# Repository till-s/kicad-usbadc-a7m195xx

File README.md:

# 130MSPS Dual-Channel Scope - Hardware Design

Please visit the [super-repository](https://github.com/till-s/ScOpen) for more information about this project.

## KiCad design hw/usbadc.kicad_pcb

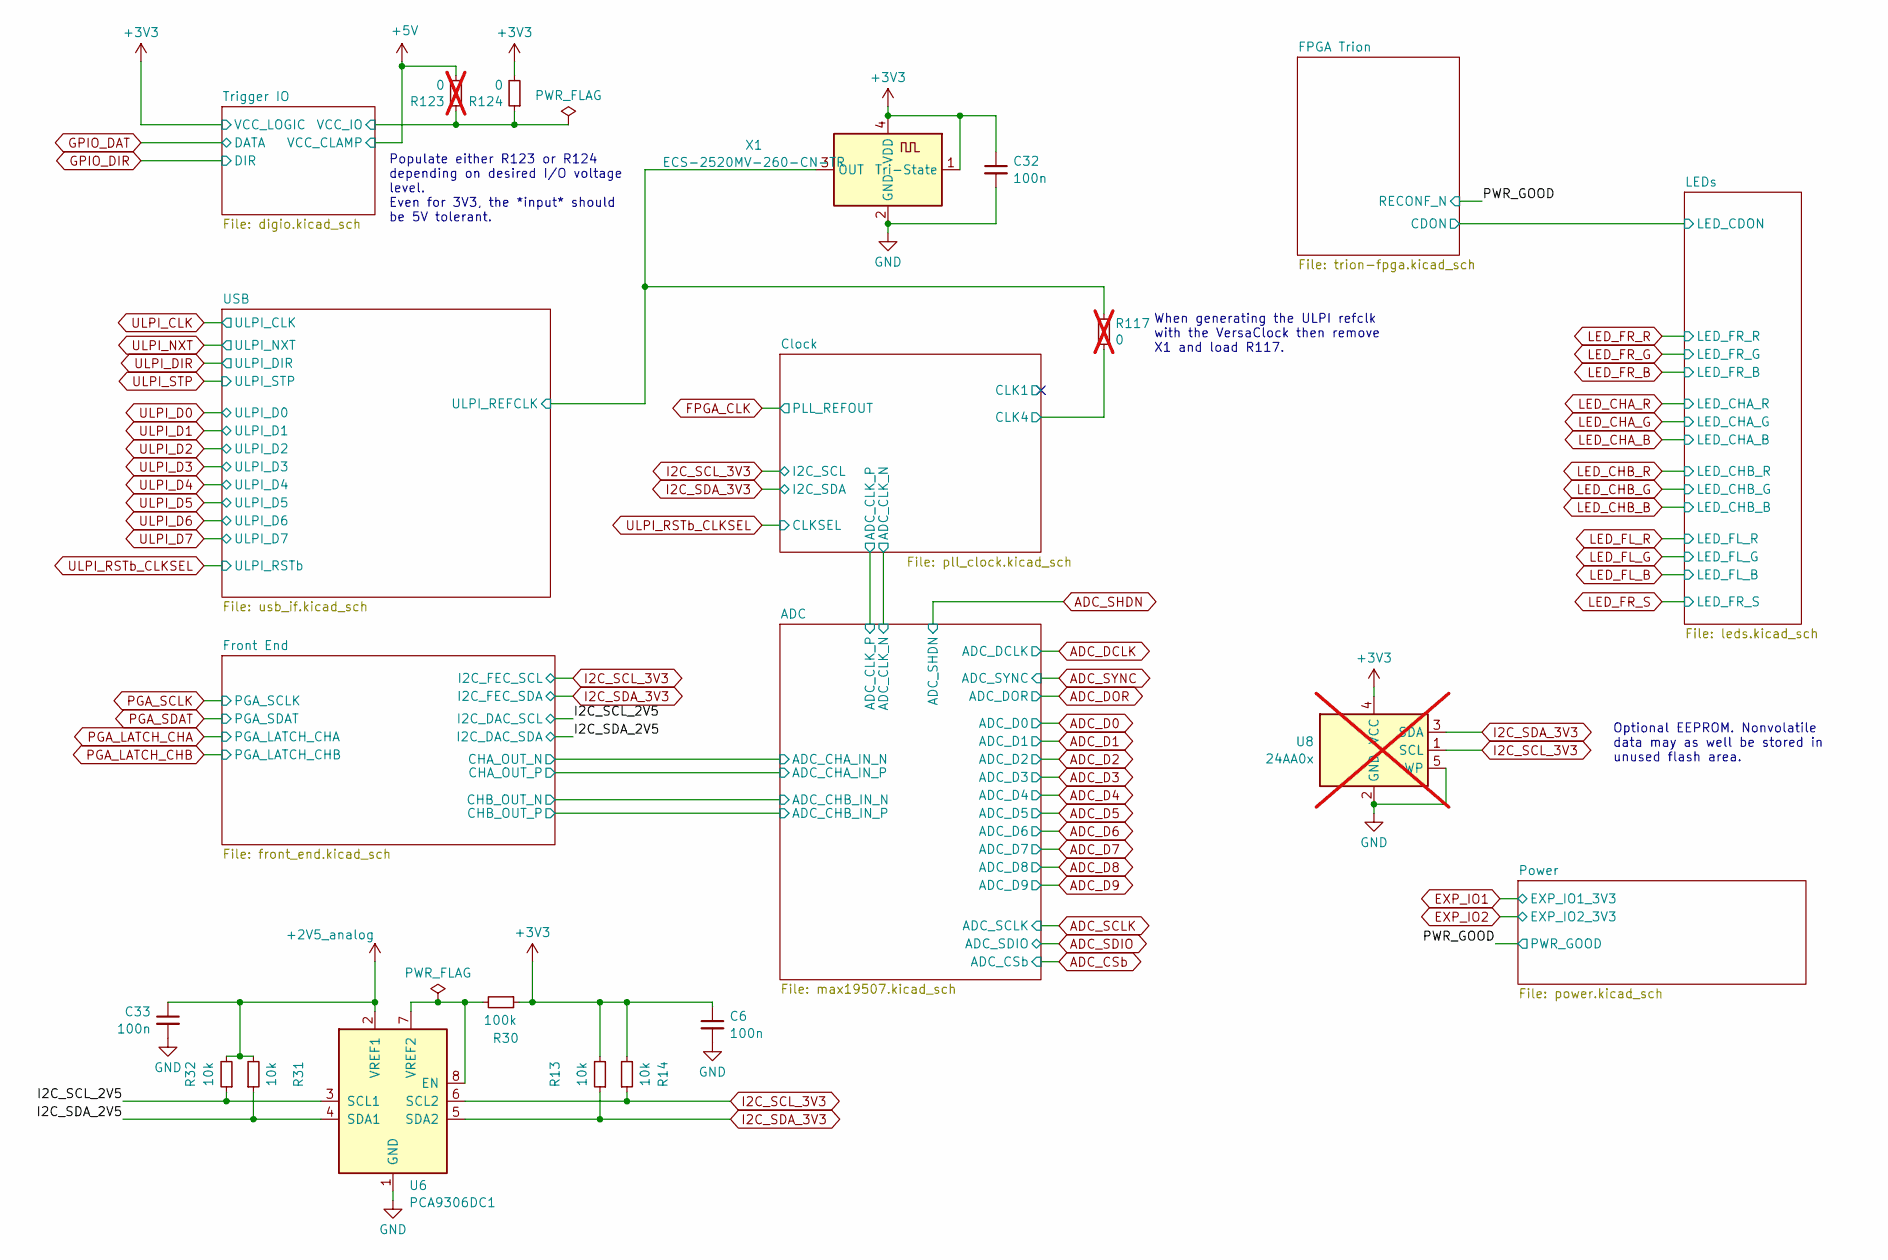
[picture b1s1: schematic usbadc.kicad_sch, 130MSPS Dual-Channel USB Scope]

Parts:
C6, C32, C33: 100n; C_0603_1608Metric; Part CL10B104KB8NFN
R13, R14, R31, R32: 10k; R_0603_1608Metric; Part RMCF0603FT10K0
R30: 100k; R_0603_1608Metric; Part RMCF0603FT100K
R117, R123: 0; R_0603_1608Metric; Part RMCF0603ZT0R00; not fitted
R124: 0; R_0603_1608Metric; Part RMCF0603ZT0R00
U6: PCA9306DC1; VSSOP-8_2.3x2mm_P0.5mm; Part PCA9306TDCURQ1
U8: 24AA0x; SOT-353_SC-70-5; Part 24AA01/LT; not fitted
X1: ECS-2520MV-260-CN-TR; Oscillator_SMD_ECS_2520MV-xxx-xx-4Pin_2.5x2.0mm; Part ECS-2520MV-260-CN-TR

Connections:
+2V5_analog: C33.1, R31.2, R32.2, U6.2 (VREF1); also elsewhere on the board
+3V3: C6.1, C32.1, R13.2, R14.2, R30.1, R124.2, U8.4 (VCC), X1.1 (Tri-State), X1.4 (VDD); also elsewhere on the board
+5V: R123.2; also elsewhere on the board
/Clock/CLK4: R117.2; also elsewhere on the board
/I2C_SCL_2V5: R32.1, U6.3 (SCL1); also elsewhere on the board
/I2C_SDA_2V5: R31.1, U6.4 (SDA1); also elsewhere on the board
/Trigger IO/VCC_IO: R123.1, R124.1; also elsewhere on the board
/USB/ULPI_REFCLK: R117.1, X1.3 (OUT); also elsewhere on the board
GND: C6.2, C32.2, C33.2, U6.1 (GND), U8.2 (GND), U8.5 (WP), X1.2 (GND); also elsewhere on the board
I2C_SCL_3V3: R14.1, U6.6 (SCL2), U8.1 (SCL); also elsewhere on the board
I2C_SDA_3V3: R13.1, U6.5 (SDA2), U8.3 (SDA); also elsewhere on the board
unnamed: R30.2, U6.7 (VREF2), U6.8 (EN)

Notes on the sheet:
Optional EEPROM. Nonvolatile data may as well be stored in unused flash area.
When generating the ULPI refclk with the VersaClock then remove X1 and load R117.
Populate either R123 or R124 depending on desired I/O voltage level. Even for 3V3, the *input* should be 5V tolerant.

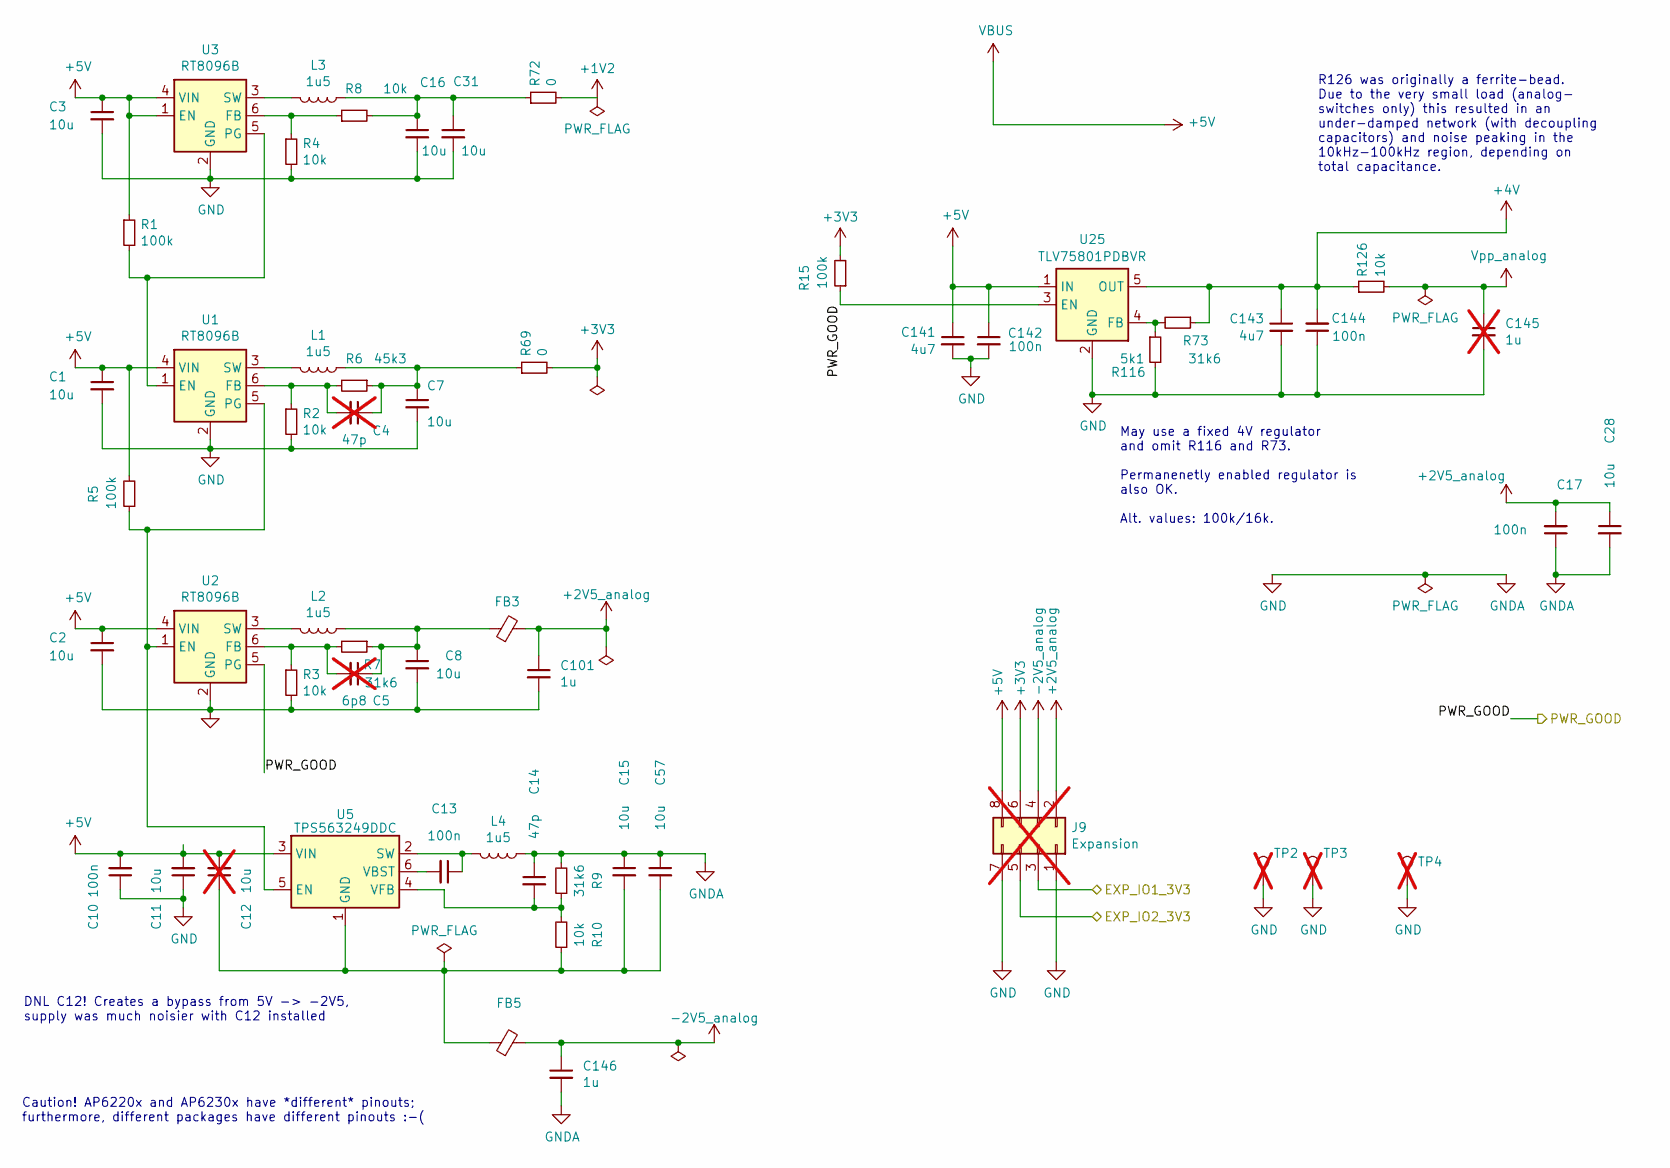
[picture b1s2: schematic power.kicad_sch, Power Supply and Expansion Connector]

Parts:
C1, C2, C3, C7, C8, C11, C15, C16, C28, C31, C57: 10u; C_1206_3216Metric; Part CL31A106KPHNNNE
C4: 47p; C_0603_1608Metric; Part 0603N470J101CT; not fitted
C5: 6p8; C_0603_1608Metric; Part 885012006050; not fitted
C10, C13, C17, C142, C144: 100n; C_0603_1608Metric; Part CL10B104KB8NFN
C12: 10u; C_1206_3216Metric; Part CL31A106KPHNNNE; not fitted
C14: 47p; C_0603_1608Metric; Part 0603N470J101CT
C101, C146: 1u; C_0805_2012Metric; Part CGA4J2X7R1C105K125AA
C141, C143: 4u7; C_0805_2012Metric; Part 2012X5R1C475K125AC
C145: 1u; C_0805_2012Metric; Part CGA4J2X7R1C105K125AA; not fitted
FB3, FB5: 600Ohm@100MHz; L_0603_1608Metric; Part MI0603J601R-10
J9: Expansion; PinHeader_2x04_P2.54mm_Vertical; not fitted
L1, L2, L3, L4: 1u5; L_1008_2520Metric; Part BDCD002520121R5MS1
R1, R5, R15: 100k; R_0603_1608Metric; Part RMCF0603FT100K
R2, R3, R4, R8, R10, R126: 10k; R_0603_1608Metric; Part RMCF0603FT10K0
R6: 45k3; R_0603_1608Metric; Part RMCF0603FT45K3
R7, R9, R73: 31k6; R_0603_1608Metric; Part RMCF0603FT31K6
R69, R72: 0; R_0603_1608Metric; Part RMCF0603ZT0R00
R116: 5k1; R_0603_1608Metric; Part RMCF0603FT5K10
TP2, TP3, TP4: TestPoint; PinHeader_1x01_P2.54mm_Vertical; not fitted
U1, U2, U3: RT8096B; SOT-23-6; Part RT8096BHGE
U5: TPS563249DDC; SOT-23-6; Part TPS563249DDCR
U25: TLV75801PDBVR; SOT-23-5; Part TLV75801PDBVR

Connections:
+1V2: R72.2; also elsewhere on the board
+2V5_analog: C17.2, C28.1, C101.1, FB3.2, J9.2; also elsewhere on the board
+3V3: J9.6, R15.2, R69.2; also elsewhere on the board
+4V: C143.1, C144.2, R73.1, R126.1, U25.5 (OUT); also elsewhere on the board
+5V: C1.1, C2.1, C3.1, C10.2, C11.2, C12.2, C141.1, C142.1, J9.8, R1.1, R5.2, U1.4 (VIN), U2.4 (VIN), U3.1 (EN), U3.4 (VIN), U5.3 (VIN), U25.1 (IN); also elsewhere on the board
-2V5_analog: C146.1, FB5.2, J9.4; also elsewhere on the board
/PWR_GOOD: R15.1, U2.5 (PG), U25.3 (EN); also elsewhere on the board
EXP_IO1: J9.3; also elsewhere on the board
EXP_IO2: J9.5; also elsewhere on the board
GND: C1.2, C2.2, C3.2, C7.2, C8.2, C10.1, C11.1, C14.1, C15.1, C16.2, C17.1, C28.2, C31.2, C57.1, C101.2, C141.2, C142.2, C143.2, C144.1, C145.2, C146.2, J9.1, J9.7, L4.1, R2.2, R3.2, R4.2, R9.2, R116.2, TP2.1, TP3.1, TP4.1, U1.2 (GND), U2.2 (GND), U3.2 (GND), U25.2 (GND); also elsewhere on the board
unnamed: C4.1, C7.1, L1.1, R6.1, R69.1
unnamed: C5.1, C8.1, FB3.1, L2.1, R7.1
unnamed: C16.1, C31.1, L3.1, R8.2, R72.1
unnamed: R1.2, U1.1 (EN), U3.5 (PG)
unnamed: C4.2, R2.1, R6.2, U1.6 (FB)
unnamed: R5.1, U1.5 (PG), U2.1 (EN), U5.5 (EN)
unnamed: L1.2, U1.3 (SW)
unnamed: C5.2, R3.1, R7.2, U2.6 (FB)
unnamed: L2.2, U2.3 (SW)
unnamed: R4.1, R8.1, U3.6 (FB)
unnamed: L3.2, U3.3 (SW)
unnamed: C12.1, C15.2, C57.2, FB5.1, R10.1, U5.1 (GND)
unnamed: C13.1, L4.2, U5.2 (SW)
unnamed: C13.2, U5.6 (VBST)
unnamed: C14.2, R9.1, R10.2, U5.4 (VFB)
unnamed: R73.2, R116.1, U25.4 (FB)
Vpp_analog: C145.1, R126.2; also elsewhere on the board

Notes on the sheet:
May use a fixed 4V regulator and omit R116 and R73. Permanenetly enabled regulator is also OK. Alt. values: 100k/16k.
R126 was originally a ferrite-bead. Due to the very small load (analog- switches only) this resulted in an under-damped network (with decoupling capacitors) and noise peaking in the 10kHz-100kHz region, depending on total capacitance.
DNL C12! Creates a bypass from 5V -> -2V5, supply was much noisier with C12 installed
Caution! AP6220x and AP6230x have *different* pinouts; furthermore, different packages have different pinouts :-(

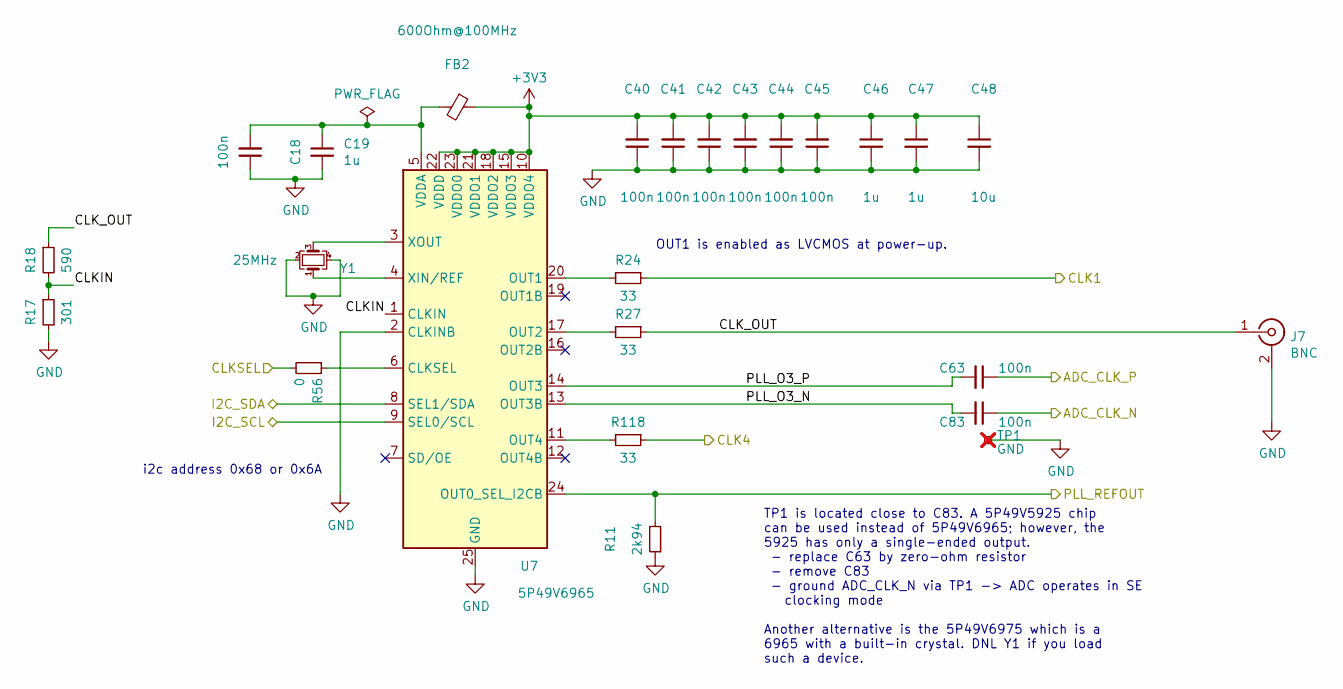
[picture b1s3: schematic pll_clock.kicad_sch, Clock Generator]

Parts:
C18, C40, C41, C42, C43, C44, C45, C63, C83: 100n; C_0603_1608Metric; Part CL10B104KB8NFN
C19, C46, C47: 1u; C_0805_2012Metric; Part CGA4J2X7R1C105K125AA
C48: 10u; C_1206_3216Metric; Part CL31A106KPHNNNE
FB2: 600Ohm@100MHz; L_0603_1608Metric; Part MI0603J601R-10
J7: BNC; BNC_Molex_0731713150; Part 0731713150
R11: 2k94; R_0603_1608Metric; Part RMCF0603FT2K94
R17: 301; R_0603_1608Metric; Part RMCF0603FT301R
R18: 590; R_0603_1608Metric; Part RMCF0603FT590R
R24, R27, R118: 33; R_0603_1608Metric; Part RMCF0603FT33R0
R56: 0; R_0603_1608Metric; Part RMCF0603ZT0R00
TP1: GND; single_pad; not fitted
U7: 5P49V6965; QFN-24-1EP_4x4mm_P0.5mm_EP2.8x2.8mm; Part 5P49V6965A000NLGI8
Y1: 25MHz; Crystal_SMD_Abracon_ABM10-4Pin_2.5x2.0mm; Part ABM10W-25.0000MHZ-8-B1U-T3

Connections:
+3V3: C40.2, C41.2, C42.2, C43.2, C44.2, C45.2, C46.1, C47.1, C48.1, FB2.1, U7.10 (VDDO4), U7.15 (VDDO3), U7.18 (VDDO2), U7.21 (VDDO1), U7.22 (VDDD), U7.23 (VDDO0); also elsewhere on the board
/ADC/ADC_CLK_N: C83.1; also elsewhere on the board
/ADC/ADC_CLK_P: C63.1; also elsewhere on the board
/Clock/CLK1: R24.1
/Clock/CLK4: R118.1; also elsewhere on the board
/Clock/CLKIN: R17.1, R18.2, U7.1 (CLKIN)
/Clock/CLK_OUT: J7.1 (In), R18.1, R27.1
/Clock/PLL_O3_N: C83.2, U7.13 (OUT3B)
/Clock/PLL_O3_P: C63.2, U7.14 (OUT3)
FPGA_CLK: R11.2, U7.24 (OUT0_SEL_I2CB); also elsewhere on the board
GND: C18.1, C19.2, C40.1, C41.1, C42.1, C43.1, C44.1, C45.1, C46.2, C47.2, C48.2, J7.2 (Ext), R11.1, R17.2, TP1.1, U7.2 (CLKINB), U7.25 (GND), Y1.2, Y1.4; also elsewhere on the board
I2C_SCL_3V3: U7.9 (SEL0/SCL); also elsewhere on the board
I2C_SDA_3V3: U7.8 (SEL1/SDA); also elsewhere on the board
unnamed: R56.1, U7.6 (CLKSEL)
unnamed: R24.2, U7.20 (OUT1)
unnamed: R27.2, U7.17 (OUT2)
unnamed: R118.2, U7.11 (OUT4)
unnamed: C18.2, C19.1, FB2.2, U7.5 (VDDA)
unnamed: U7.4 (XIN/REF), Y1.1
unnamed: U7.3 (XOUT), Y1.3
ULPI_RSTb_CLKSEL: R56.2; also elsewhere on the board

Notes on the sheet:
TP1 is located close to C83. A 5P49V5925 chip can be used instead of 5P49V6965; however, the 5925 has only a single-ended output. - replace C63 by zero-ohm resistor - remove C83 - ground ADC_CLK_N via TP1 -> ADC operates in SE clocking mode Another alternative is the 5P49V6975 which is a 6965 with 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
i2c address 0x68 or 0x6A
OUT1 is enabled as LVCMOS at power-up.

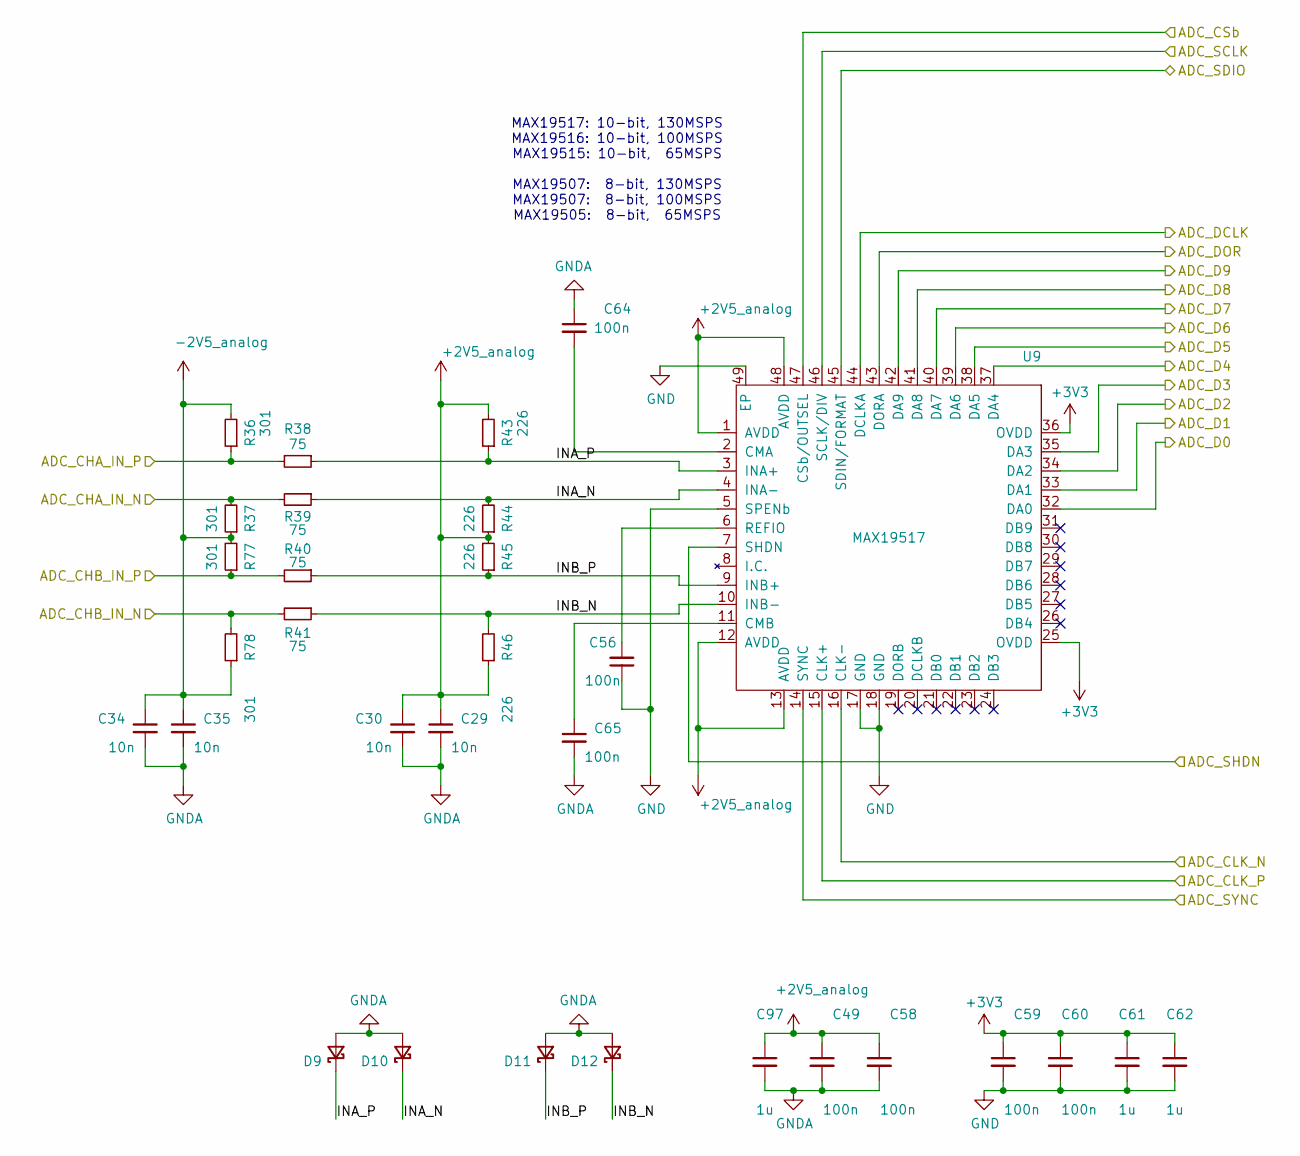
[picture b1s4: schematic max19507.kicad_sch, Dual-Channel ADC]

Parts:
C29, C30, C34, C35: 10n; C_0603_1608Metric; Part C0603C103J5RACTU
C49, C58, C59, C60: 100n; C_0402_1005Metric; Part C1005X7R1E104K050BB
C56, C64, C65: 100n; C_0603_1608Metric; Part CL10B104KB8NFN
C61, C62, C97: 1u; C_0805_2012Metric; Part CGA4J2X7R1C105K125AA
D9, D10, D11, D12: NSR0170HT1G; D_SOD-323; Part NSR0170HT1G
R36, R37, R77, R78: 301; R_0603_1608Metric; Part RMCF0603FT301R
R38, R39, R40, R41: 75; R_0603_1608Metric; Part RMCF0603FT75R0
R43, R44, R45, R46: 226; R_0603_1608Metric; Part RMCF0603FT226R
U9: MAX19517; QFN-48-1EP_7x7mm_P0.5mm_EP5.6x5.6mm_ThermalVias_biggerholes; Part MAX19517ETM+

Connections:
+2V5_analog: C29.1, C30.1, C49.1, C58.1, C97.1, R43.2, R44.1, R45.2, R46.1, U9.1 (AVDD), U9.12 (AVDD), U9.13 (AVDD), U9.48 (AVDD); also elsewhere on the board
+3V3: C59.1, C60.1, C61.1, C62.1, U9.25 (OVDD), U9.36 (OVDD); also elsewhere on the board
-2V5_analog: C34.1, C35.1, R36.2, R37.1, R77.2, R78.1; also elsewhere on the board
/ADC/ADC_CHA_IN_N: R37.2, R39.2; also elsewhere on the board
/ADC/ADC_CHA_IN_P: R36.1, R38.2; also elsewhere on the board
/ADC/ADC_CHB_IN_N: R41.2, R78.2; also elsewhere on the board
/ADC/ADC_CHB_IN_P: R40.2, R77.1; also elsewhere on the board
/ADC/ADC_CLK_N: U9.16 (CLK-); also elsewhere on the board
/ADC/ADC_CLK_P: U9.15 (CLK+); also elsewhere on the board
/ADC/INA_N: D10.1 (K), R39.1, R44.2, U9.4 (INA-)
/ADC/INA_P: D9.1 (K), R38.1, R43.1, U9.3 (INA+)
/ADC/INB_N: D12.1 (K), R41.1, R46.2, U9.10 (INB-)
/ADC/INB_P: D11.1 (K), R40.1, R45.1, U9.9 (INB+)
ADC_CSb: U9.47 (CSb/OUTSEL); also elsewhere on the board
ADC_D0: U9.32 (DA0); also elsewhere on the board
ADC_D1: U9.33 (DA1); also elsewhere on the board
ADC_D2: U9.34 (DA2); also elsewhere on the board
ADC_D3: U9.35 (DA3); also elsewhere on the board
ADC_D4: U9.37 (DA4); also elsewhere on the board
ADC_D5: U9.38 (DA5); also elsewhere on the board
ADC_D6: U9.39 (DA6); also elsewhere on the board
ADC_D7: U9.40 (DA7); also elsewhere on the board
ADC_D8: U9.41 (DA8); also elsewhere on the board
ADC_D9: U9.42 (DA9); also elsewhere on the board
ADC_DCLK: U9.44 (DCLKA); also elsewhere on the board
ADC_DOR: U9.43 (DORA); also elsewhere on the board
ADC_SCLK: U9.46 (SCLK/DIV); also elsewhere on the board
ADC_SDIO: U9.45 (SDIN/FORMAT); also elsewhere on the board
ADC_SHDN: U9.7 (SHDN); also elsewhere on the board
ADC_SYNC: U9.14 (SYNC); also elsewhere on the board
GND: C29.2, C30.2, C34.2, C35.2, C49.2, C56.1, C58.2, C59.2, C60.2, C61.2, C62.2, C64.1, C65.2, C97.2, D9.2 (A), D10.2 (A), D11.2 (A), D12.2 (A), U9.5 (SPENb), U9.17 (GND), U9.18 (GND), U9.49 (EP); also elsewhere on the board
unnamed: C64.2, U9.2 (CMA)
unnamed: C65.1, U9.11 (CMB)
unnamed: C56.2, U9.6 (REFIO)

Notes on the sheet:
MAX19517: 10-bit, 130MSPS MAX19516: 10-bit, 100MSPS MAX19515: 10-bit, 65MSPS MAX19507: 8-bit, 130MSPS MAX19507: 8-bit, 100MSPS MAX19505: 8-bit, 65MSPS

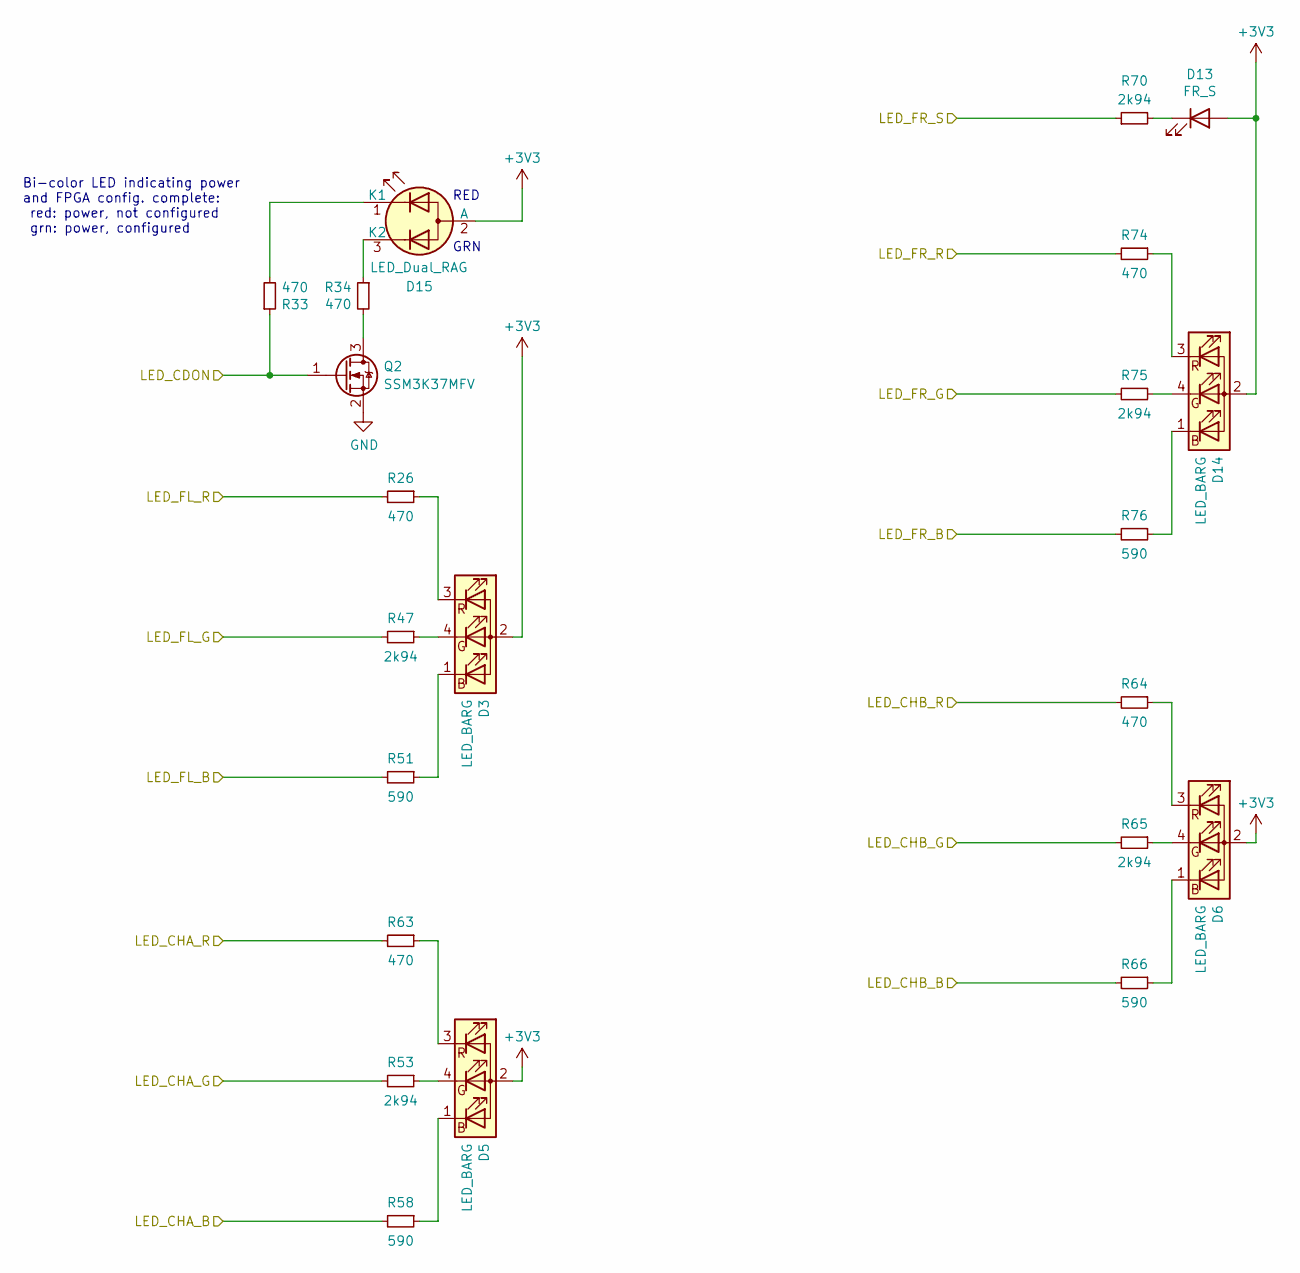
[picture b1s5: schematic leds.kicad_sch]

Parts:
D3, D5, D6, D14: LED_BARG; LED_RGB_2504_horiz_barg; Part APFA2507QBDSEEZGKC
D13: FR_S; LED_0603_1608Metric_reduced_cyrd; Part 155060GS75300
D15: LED_Dual_RAG; LED_Wuerth_Sideview; Part 155124RV73200
Q2: SSM3K37MFV; SOT-723; Part SSM3K37MFV
R26, R33, R34, R63, R64, R74: 470; R_0603_1608Metric; Part RMCF0603FT470R
R47, R53, R65, R75: 2k94; R_0603_1608Metric; Part RMCF0603FT2K94
R51, R58, R66, R76: 590; R_0603_1608Metric; Part RMCF0603FT590R
R70: 2k94; R_0603_1608Metric; Part RMCF0603FT470R

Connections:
+3V3: D3.2 (A), D5.2 (A), D6.2 (A), D13.2 (A), D14.2 (A), D15.2 (A); also elsewhere on the board
/FPGA Trion/CDON: Q2.1 (G), R33.1; also elsewhere on the board
GND: Q2.2 (S); also elsewhere on the board
LED_CHA_B: R58.2; also elsewhere on the board
LED_CHA_G: R53.2; also elsewhere on the board
LED_CHA_R: R63.2; also elsewhere on the board
LED_CHB_B: R66.2; also elsewhere on the board
LED_CHB_G: R65.2; also elsewhere on the board
LED_CHB_R: R64.2; also elsewhere on the board
LED_FL_B: R51.2; also elsewhere on the board
LED_FL_G: R47.2; also elsewhere on the board
LED_FL_R: R26.2; also elsewhere on the board
LED_FR_B: R76.2; also elsewhere on the board
LED_FR_G: R75.2; also elsewhere on the board
LED_FR_R: R74.2; also elsewhere on the board
LED_FR_S: R70.1; also elsewhere on the board
unnamed: D3.1 (BK), R51.1
unnamed: D3.4 (GK), R47.1
unnamed: D3.3 (RK), R26.1
unnamed: D5.1 (BK), R58.1
unnamed: D5.4 (GK), R53.1
unnamed: D5.3 (RK), R63.1
unnamed: D6.1 (BK), R66.1
unnamed: D6.4 (GK), R65.1
unnamed: D6.3 (RK), R64.1
unnamed: D13.1 (K), R70.2
unnamed: D14.1 (BK), R76.1
unnamed: D14.4 (GK), R75.1
unnamed: D14.3 (RK), R74.1
unnamed: D15.1 (K1), R33.2
unnamed: D15.3 (K2), R34.1
unnamed: Q2.3 (D), R34.2

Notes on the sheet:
RED
GRN
Bi-color LED indicating power and FPGA config. complete: red: power, not configured grn: power, configured

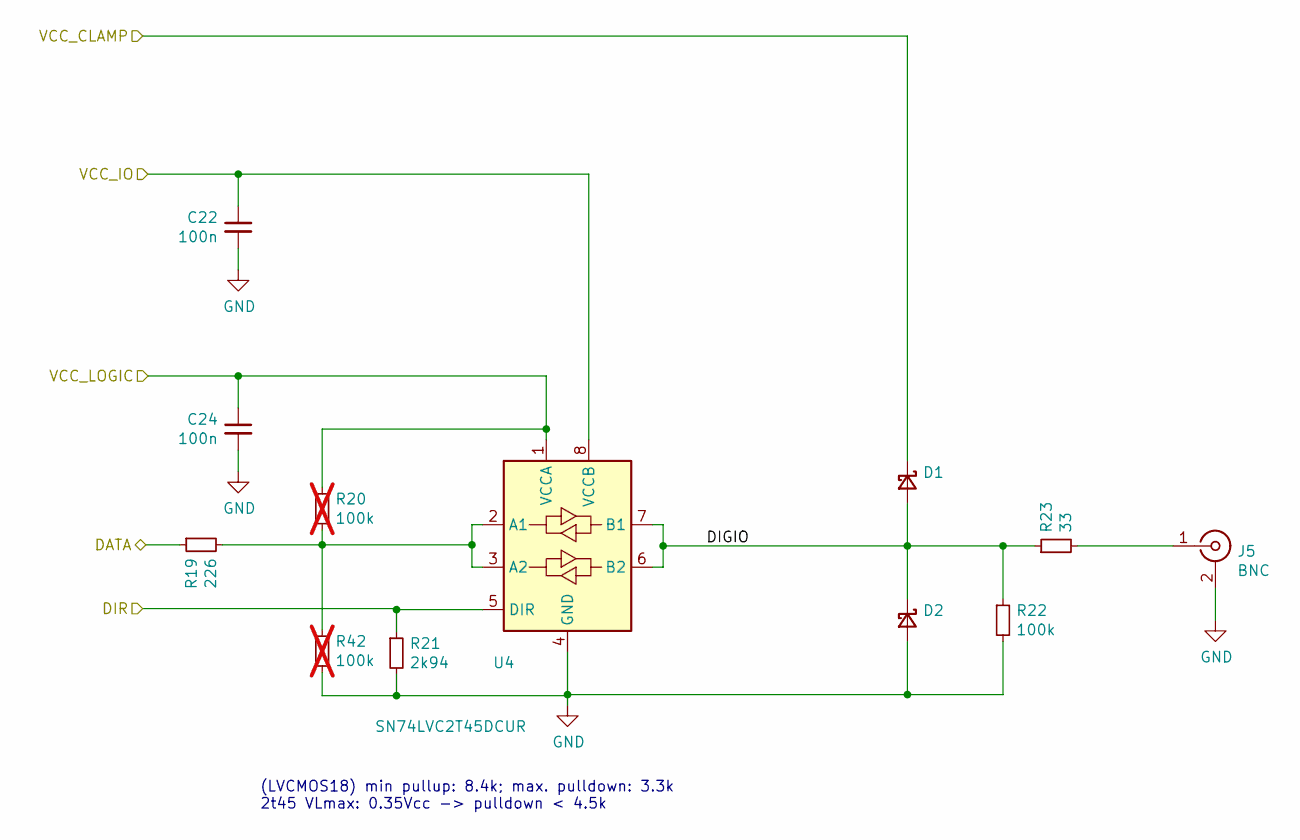
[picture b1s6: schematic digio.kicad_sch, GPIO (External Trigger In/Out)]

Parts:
C22, C24: 100n; C_0603_1608Metric; Part CL10B104KB8NFN
D1, D2: NSR0170HT1G; D_SOD-323; Part NSR0170HT1G
J5: BNC; BNC_Molex_0731713150; Part 0731713150
R19: 226; R_0603_1608Metric; Part RMCF0603FT226R
R20, R42: 100k; R_0603_1608Metric; Part RMCF0603FT100K; not fitted
R21: 2k94; R_0603_1608Metric; Part RMCF0603FT2K94
R22: 100k; R_0603_1608Metric; Part RMCF0603FT100K
R23: 33; R_0603_1608Metric; Part RMCF0603FT33R0
U4: SN74LVC2T45DCUR; VSSOP-8_2.3x2mm_P0.5mm; Part 74LVC2T45DC,125

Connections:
+3V3: C24.1, R20.1, U4.1 (VCCA); also elsewhere on the board
+5V: D1.1 (K); also elsewhere on the board
/Trigger IO/DIGIO: D1.2 (A), D2.1 (K), R22.1, R23.1, U4.6 (B2), U4.7 (B1)
/Trigger IO/VCC_IO: C22.1, U4.8 (VCCB); also elsewhere on the board
GND: C22.2, C24.2, D2.2 (A), J5.2 (Ext), R21.2, R22.2, R42.2, U4.4 (GND); also elsewhere on the board
GPIO_DAT: R19.1; also elsewhere on the board
GPIO_DIR: R21.1, U4.5 (DIR); also elsewhere on the board
unnamed: J5.1 (In), R23.2
unnamed: R19.2, R20.2, R42.1, U4.2 (A1), U4.3 (A2)

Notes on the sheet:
(LVCMOS18) min pullup: 8.4k; max. pulldown: 3.3k 2t45 VLmax: 0.35Vcc -> pulldown < 4.5k

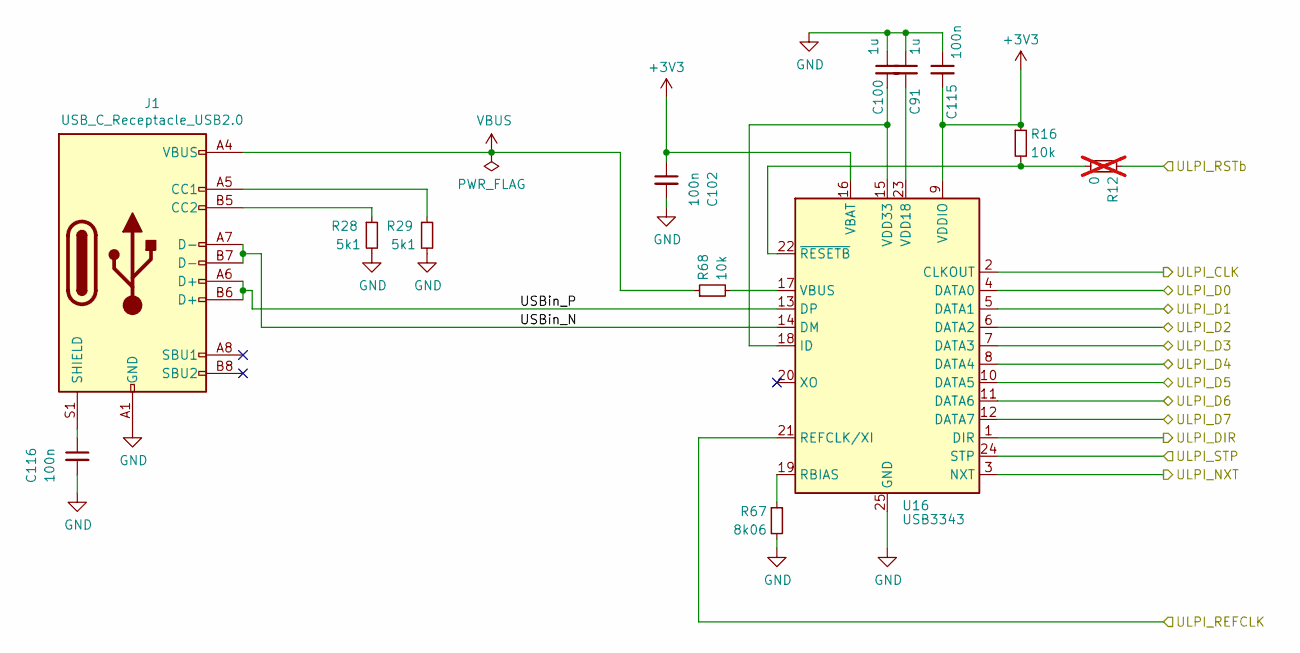
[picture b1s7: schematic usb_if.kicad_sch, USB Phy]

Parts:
C91, C100: 1u; C_0603_1608Metric; Part CL10B104KB8NFNC
C102, C115, C116: 100n; C_0603_1608Metric; Part CL10B104KB8NFN
J1: USB_C_Receptacle_USB2.0; USB_C_Receptacle_Molex_2171790001_16P_TopMnt_Horizontal; Part 2171790001
R12: 0; R_0603_1608Metric; Part RMCF0603ZT0R00; not fitted
R16, R68: 10k; R_0603_1608Metric; Part RMCF0603FT10K0
R28, R29: 5k1; R_0603_1608Metric; Part RMCF0603FT5K10
R67: 8k06; R_0603_1608Metric; Part RMCF0603FT8K06
U16: USB3343; QFN-24-1EP_4x4mm_P0.5mm_EP2.6x2.6mm; Part USB3343-CP-TR

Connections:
+3V3: C102.1, C115.2, R16.1, U16.9 (VDDIO), U16.16 (VBAT); also elsewhere on the board
+5V: J1.A4 (VBUS), J1.A9 (VBUS), J1.B4 (VBUS), J1.B9 (VBUS), R68.1; also elsewhere on the board
/USB/ULPI_REFCLK: U16.21 (REFCLK/XI); also elsewhere on the board
/USB/USBin_N: J1.A7 (D-), J1.B7 (D-), U16.14 (DM)
/USB/USBin_P: J1.A6 (D+), J1.B6 (D+), U16.13 (DP)
GND: C91.1, C100.1, C102.2, C115.1, C116.2, J1.A1 (GND), J1.A12 (GND), J1.B1 (GND), J1.B12 (GND), R28.2, R29.2, R67.2, U16.25 (GND); also elsewhere on the board
unnamed: J1.A5 (CC1), R29.1
unnamed: J1.B5 (CC2), R28.1
unnamed: C116.1, J1.S1 (SHIELD)
unnamed: C100.2, U16.15 (VDD33), U16.18 (ID)
unnamed: R67.1, U16.19 (RBIAS)
unnamed: R68.2, U16.17 (VBUS)
unnamed: C91.2, U16.23 (VDD18)
unnamed: R12.2, R16.2, U16.22 (~RESETB)
ULPI_CLK: U16.2 (CLKOUT); also elsewhere on the board
ULPI_D0: U16.4 (DATA0); also elsewhere on the board
ULPI_D1: U16.5 (DATA1); also elsewhere on the board
ULPI_D2: U16.6 (DATA2); also elsewhere on the board
ULPI_D3: U16.7 (DATA3); also elsewhere on the board
ULPI_D4: U16.8 (DATA4); also elsewhere on the board
ULPI_D5: U16.10 (DATA5); also elsewhere on the board
ULPI_D6: U16.11 (DATA6); also elsewhere on the board
ULPI_D7: U16.12 (DATA7); also elsewhere on the board
ULPI_DIR: U16.1 (DIR); also elsewhere on the board
ULPI_NXT: U16.3 (NXT); also elsewhere on the board
ULPI_RSTb_CLKSEL: R12.1; also elsewhere on the board
ULPI_STP: U16.24 (STP); also elsewhere on the board

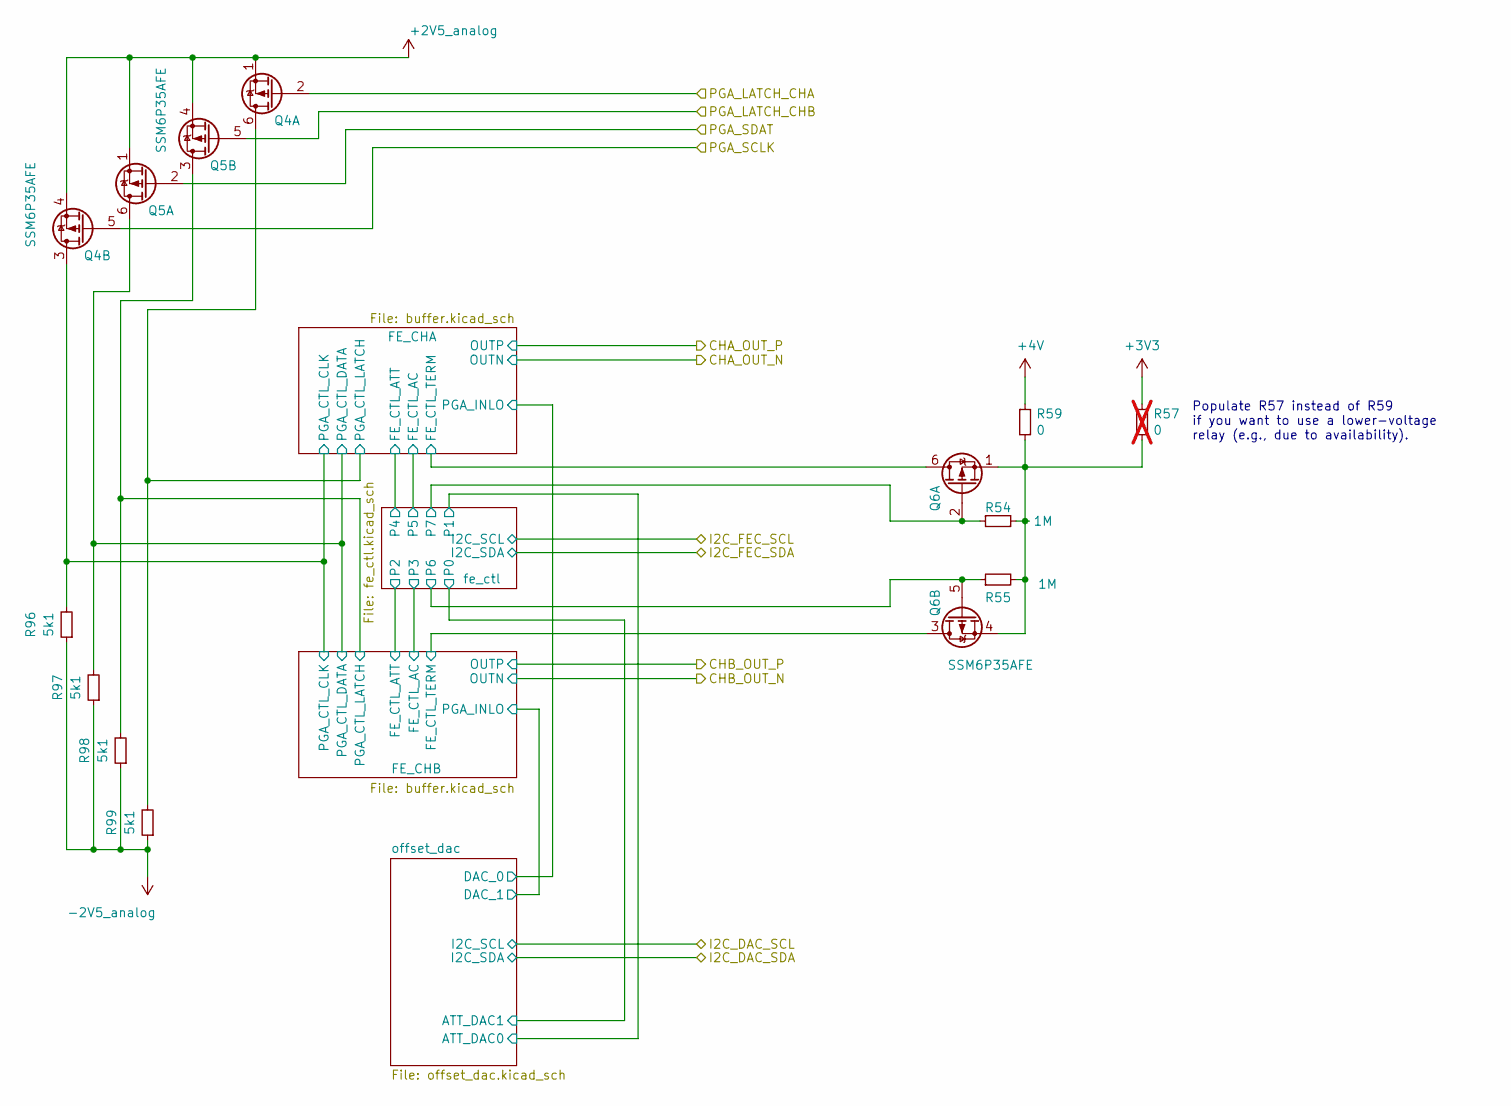
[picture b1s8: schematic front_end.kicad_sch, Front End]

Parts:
Q4, Q5, Q6: SSM6P35AFE; SOT-563-adjusted; Part SSM6P35AFE
R54, R55: 1M; R_0603_1608Metric; Part RMCF0603FT1M00
R57: 0; R_0603_1608Metric; Part RMCF0603ZT0R00; not fitted
R59: 0; R_0603_1608Metric; Part RMCF0603ZT0R00
R96, R97, R98, R99: 5k1; R_0603_1608Metric; Part RMCF0603FT5K10

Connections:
+2V5_analog: Q4.1 (S), Q4.4 (S), Q5.1 (S), Q5.4 (S); also elsewhere on the board
+3V3: R57.1; also elsewhere on the board
+4V: R59.1; also elsewhere on the board
-2V5_analog: R96.1, R97.1, R98.1, R99.1; also elsewhere on the board
/Front End/FE_CHA/FE_CTL_TERM: Q6.6 (D); also elsewhere on the board
/Front End/FE_CHA/PGA_CTL_CLK: Q4.3 (D), R96.2; also elsewhere on the board
/Front End/FE_CHA/PGA_CTL_DATA: Q5.6 (D), R97.2; also elsewhere on the board
/Front End/FE_CHA/PGA_CTL_LATCH: Q4.6 (D), R99.2; also elsewhere on the board
/Front End/FE_CHB/FE_CTL_TERM: Q6.3 (D); also elsewhere on the board
/Front End/FE_CHB/PGA_CTL_LATCH: Q5.3 (D), R98.2; also elsewhere on the board
/Front End/fe_ctl/P6: Q6.5 (G), R55.1; also elsewhere on the board
/Front End/fe_ctl/P7: Q6.2 (G), R54.1; also elsewhere on the board
unnamed: Q6.1 (S), Q6.4 (S), R54.2, R55.2, R57.2, R59.2
PGA_LATCH_CHA: Q4.2 (G); also elsewhere on the board
PGA_LATCH_CHB: Q5.5 (G); also elsewhere on the board
PGA_SCLK: Q4.5 (G); also elsewhere on the board
PGA_SDAT: Q5.2 (G); also elsewhere on the board

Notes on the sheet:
Populate R57 instead of R59 if you want to use a lower-voltage relay (e.g., due to availability).

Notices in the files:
hw/bank_1a_cfg.kicad_sch:
Copyright Till Straumann, 2025
License: CERN-OHL-P v2
